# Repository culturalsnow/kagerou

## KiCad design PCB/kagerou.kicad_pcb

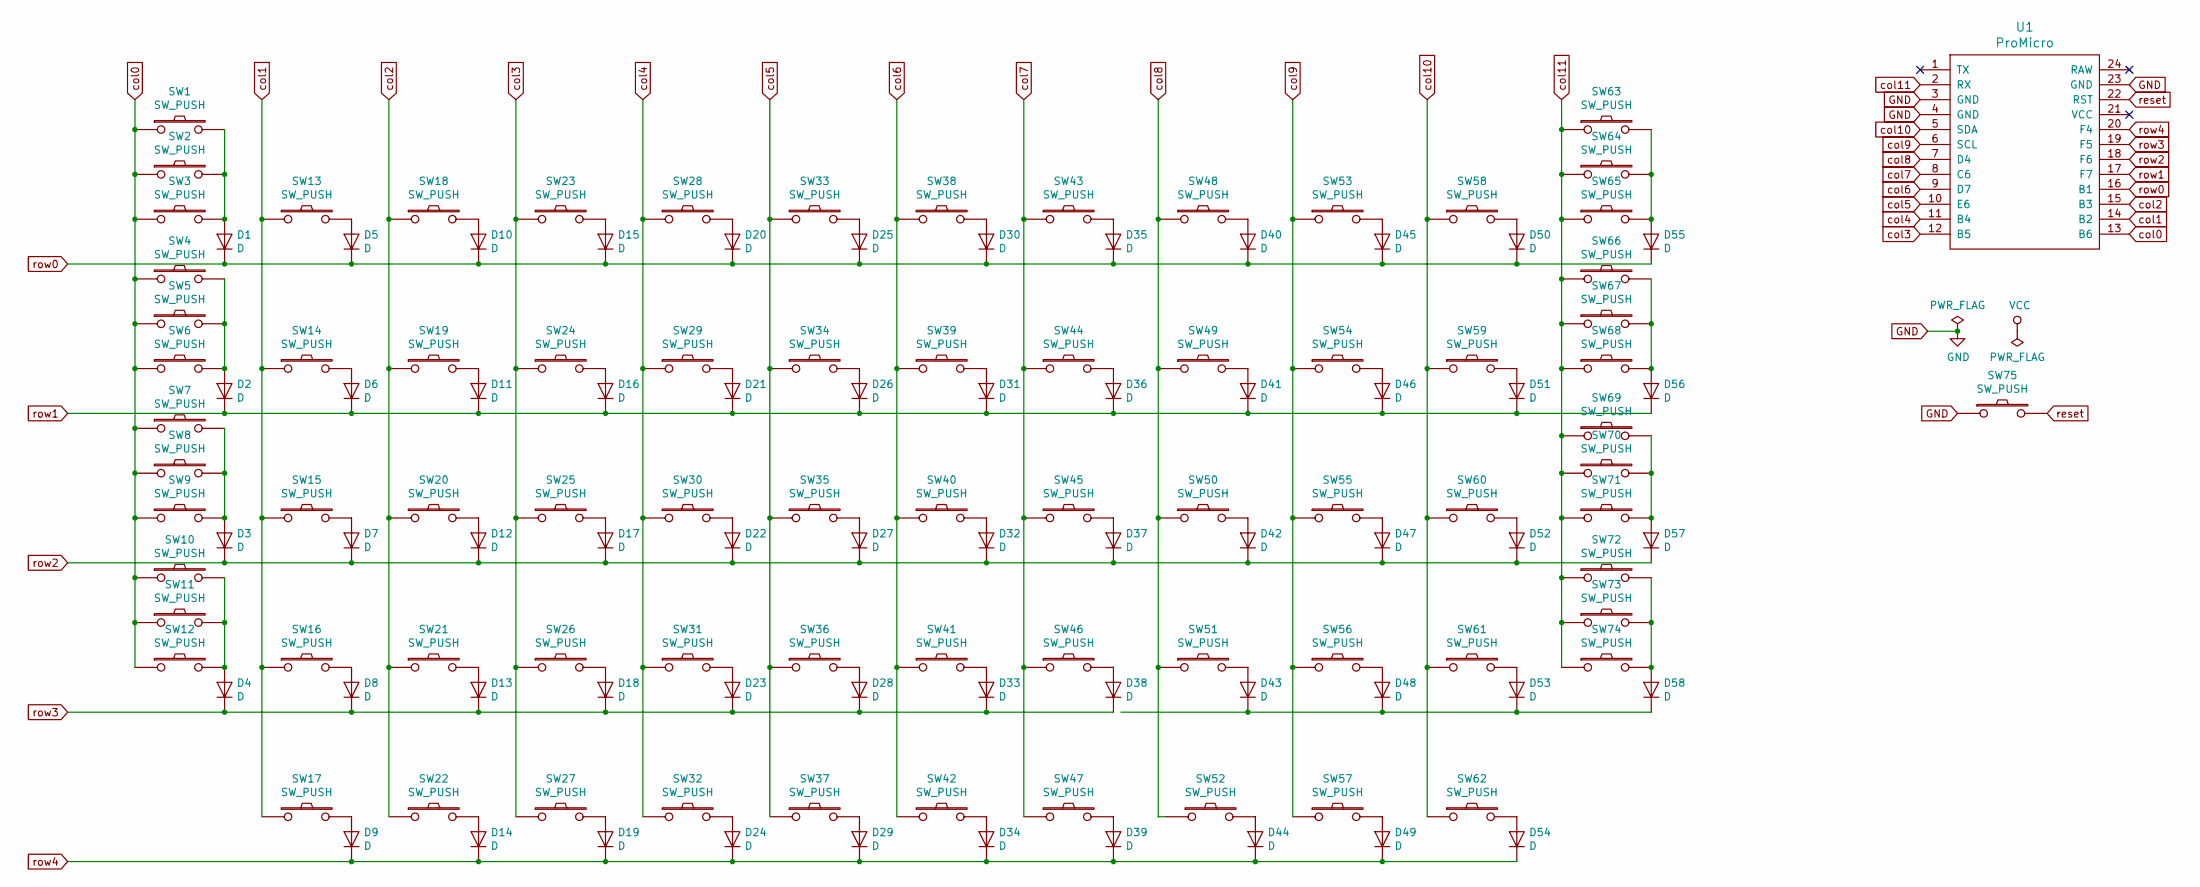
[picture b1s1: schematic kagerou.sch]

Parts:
D1, D2, D3, D4, D5, D6, D7, D8, D9, D10, D11, D12, D13, D14, D15, D16, D17, D18, D19, D20, D21, D22, D23, D24, D25, D26, D27, D28, D29, D30, D31, D32, D33, D34, D35, D36, D37, D38, D39, D40, D41, D42, D43, D44, D45, D46, D47, D48, D49, D50, D51, D52, D53, D54, D55, D56, D57, D58: D; D_SOD-123
SW1, SW2, SW4, SW5, SW7, SW8, SW10, SW11, SW13, SW14, SW15, SW16, SW17, SW18, SW19, SW20, SW21, SW22, SW23, SW24, SW25, SW26, SW27, SW28, SW29, SW30, SW31, SW32, SW33, SW34, SW35, SW36, SW38, SW39, SW40, SW41, SW43, SW44, SW45, SW46, SW47, SW48, SW49, SW50, SW51, SW52, SW53, SW54, SW55, SW56, SW57, SW58, SW59, SW60, SW61, SW62, SW63, SW64, SW66, SW67, SW69, SW70, SW72, SW73: SW_PUSH; MX_Plate_100H
SW3, SW6, SW9, SW12, SW37, SW42, SW65, SW68, SW71, SW74: SW_PUSH; MX_Plate_200H
SW75: SW_PUSH; ResetSW_4P
U1: ProMicro; ProMicro_v2_Backside

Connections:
GND: SW75.1, U1.3 (GND), U1.4 (GND), U1.23 (GND)
unnamed: D1.2 (A), SW1.2, SW2.2, SW3.2
unnamed: D2.2 (A), SW4.2, SW5.2, SW6.2
unnamed: D3.2 (A), SW7.2, SW8.2, SW9.2
unnamed: D4.2 (A), SW10.2, SW11.2, SW12.2
unnamed: D5.2 (A), SW13.2
unnamed: D6.2 (A), SW14.2
unnamed: D7.2 (A), SW15.2
unnamed: D8.2 (A), SW16.2
unnamed: D9.2 (A), SW17.2
unnamed: D10.2 (A), SW18.2
unnamed: D11.2 (A), SW19.2
unnamed: D12.2 (A), SW20.2
unnamed: D13.2 (A), SW21.2
unnamed: D14.2 (A), SW22.2
unnamed: D15.2 (A), SW23.2
unnamed: D16.2 (A), SW24.2
unnamed: D17.2 (A), SW25.2
unnamed: D18.2 (A), SW26.2
unnamed: D19.2 (A), SW27.2
unnamed: D20.2 (A), SW28.2
unnamed: D21.2 (A), SW29.2
unnamed: D22.2 (A), SW30.2
unnamed: D23.2 (A), SW31.2
unnamed: D24.2 (A), SW32.2
unnamed: D25.2 (A), SW33.2
unnamed: D26.2 (A), SW34.2
unnamed: D27.2 (A), SW35.2
unnamed: D28.2 (A), SW36.2
unnamed: D29.2 (A), SW37.2
unnamed: D30.2 (A), SW38.2
unnamed: D31.2 (A), SW39.2
unnamed: D32.2 (A), SW40.2
unnamed: D33.2 (A), SW41.2
unnamed: D34.2 (A), SW42.2
unnamed: D35.2 (A), SW43.2
unnamed: D36.2 (A), SW44.2
unnamed: D37.2 (A), SW45.2
unnamed: D38.2 (A), SW46.2
unnamed: D39.2 (A), SW47.2
unnamed: D40.2 (A), SW48.2
unnamed: D41.2 (A), SW49.2
unnamed: D42.2 (A), SW50.2
unnamed: D43.1 (K), D48.1 (K), D53.1 (K), D58.1 (K)
unnamed: D43.2 (A), SW51.2
unnamed: D44.2 (A), SW52.2
unnamed: D45.2 (A), SW53.2
unnamed: D46.2 (A), SW54.2
unnamed: D47.2 (A), SW55.2
unnamed: D48.2 (A), SW56.2
unnamed: D49.2 (A), SW57.2
unnamed: D50.2 (A), SW58.2
unnamed: D51.2 (A), SW59.2
unnamed: D52.2 (A), SW60.2
unnamed: D53.2 (A), SW61.2
unnamed: D54.2 (A), SW62.2
unnamed: D55.2 (A), SW63.2, SW64.2, SW65.2
unnamed: D56.2 (A), SW66.2, SW67.2, SW68.2
unnamed: D57.2 (A), SW69.2, SW70.2, SW71.2
unnamed: D58.2 (A), SW72.2, SW73.2, SW74.2
col0: SW1.1, SW2.1, SW3.1, SW4.1, SW5.1, SW6.1, SW7.1, SW8.1, SW9.1, SW10.1, SW11.1, SW12.1, U1.13 (B6)
col1: SW13.1, SW14.1, SW15.1, SW16.1, SW17.1, U1.14 (B2)
col2: SW18.1, SW19.1, SW20.1, SW21.1, SW22.1, U1.15 (B3)
col3: SW23.1, SW24.1, SW25.1, SW26.1, SW27.1, U1.12 (B5)
col4: SW28.1, SW29.1, SW30.1, SW31.1, SW32.1, U1.11 (B4)
col5: SW33.1, SW34.1, SW35.1, SW36.1, SW37.1, U1.10 (E6)
col6: SW38.1, SW39.1, SW40.1, SW41.1, SW42.1, U1.9 (D7)
col7: SW43.1, SW44.1, SW45.1, SW46.1, SW47.1, U1.8 (C6)
col8: SW48.1, SW49.1, SW50.1, SW51.1, SW52.1, U1.7 (D4)
col9: SW53.1, SW54.1, SW55.1, SW56.1, SW57.1, U1.6 (SCL)
col10: SW58.1, SW59.1, SW60.1, SW61.1, SW62.1, U1.5 (SDA)
col11: SW63.1, SW64.1, SW65.1, SW66.1, SW67.1, SW68.1, SW69.1, SW70.1, SW71.1, SW72.1, SW73.1, SW74.1, U1.2 (RX)
reset: SW75.2, U1.22 (RST)
row0: D1.1 (K), D5.1 (K), D10.1 (K), D15.1 (K), D20.1 (K), D25.1 (K), D30.1 (K), D35.1 (K), D40.1 (K), D45.1 (K), D50.1 (K), D55.1 (K), U1.16 (B1)
row1: D2.1 (K), D6.1 (K), D11.1 (K), D16.1 (K), D21.1 (K), D26.1 (K), D31.1 (K), D36.1 (K), D41.1 (K), D46.1 (K), D51.1 (K), D56.1 (K), U1.17 (F7)
row2: D3.1 (K), D7.1 (K), D12.1 (K), D17.1 (K), D22.1 (K), D27.1 (K), D32.1 (K), D37.1 (K), D42.1 (K), D47.1 (K), D52.1 (K), D57.1 (K), U1.18 (F6)
row3: D4.1 (K), D8.1 (K), D13.1 (K), D18.1 (K), D23.1 (K), D28.1 (K), D33.1 (K), D38.1 (K), U1.19 (F5)
row4: D9.1 (K), D14.1 (K), D19.1 (K), D24.1 (K), D29.1 (K), D34.1 (K), D39.1 (K), D44.1 (K), D49.1 (K), D54.1 (K), U1.20 (F4)

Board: 2 copper layers, 134 parts (0 on the bottom side), 78 nets, no tracks yet.

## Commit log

2019-03-14 pcb outline
2019-03-14 pcb schema
